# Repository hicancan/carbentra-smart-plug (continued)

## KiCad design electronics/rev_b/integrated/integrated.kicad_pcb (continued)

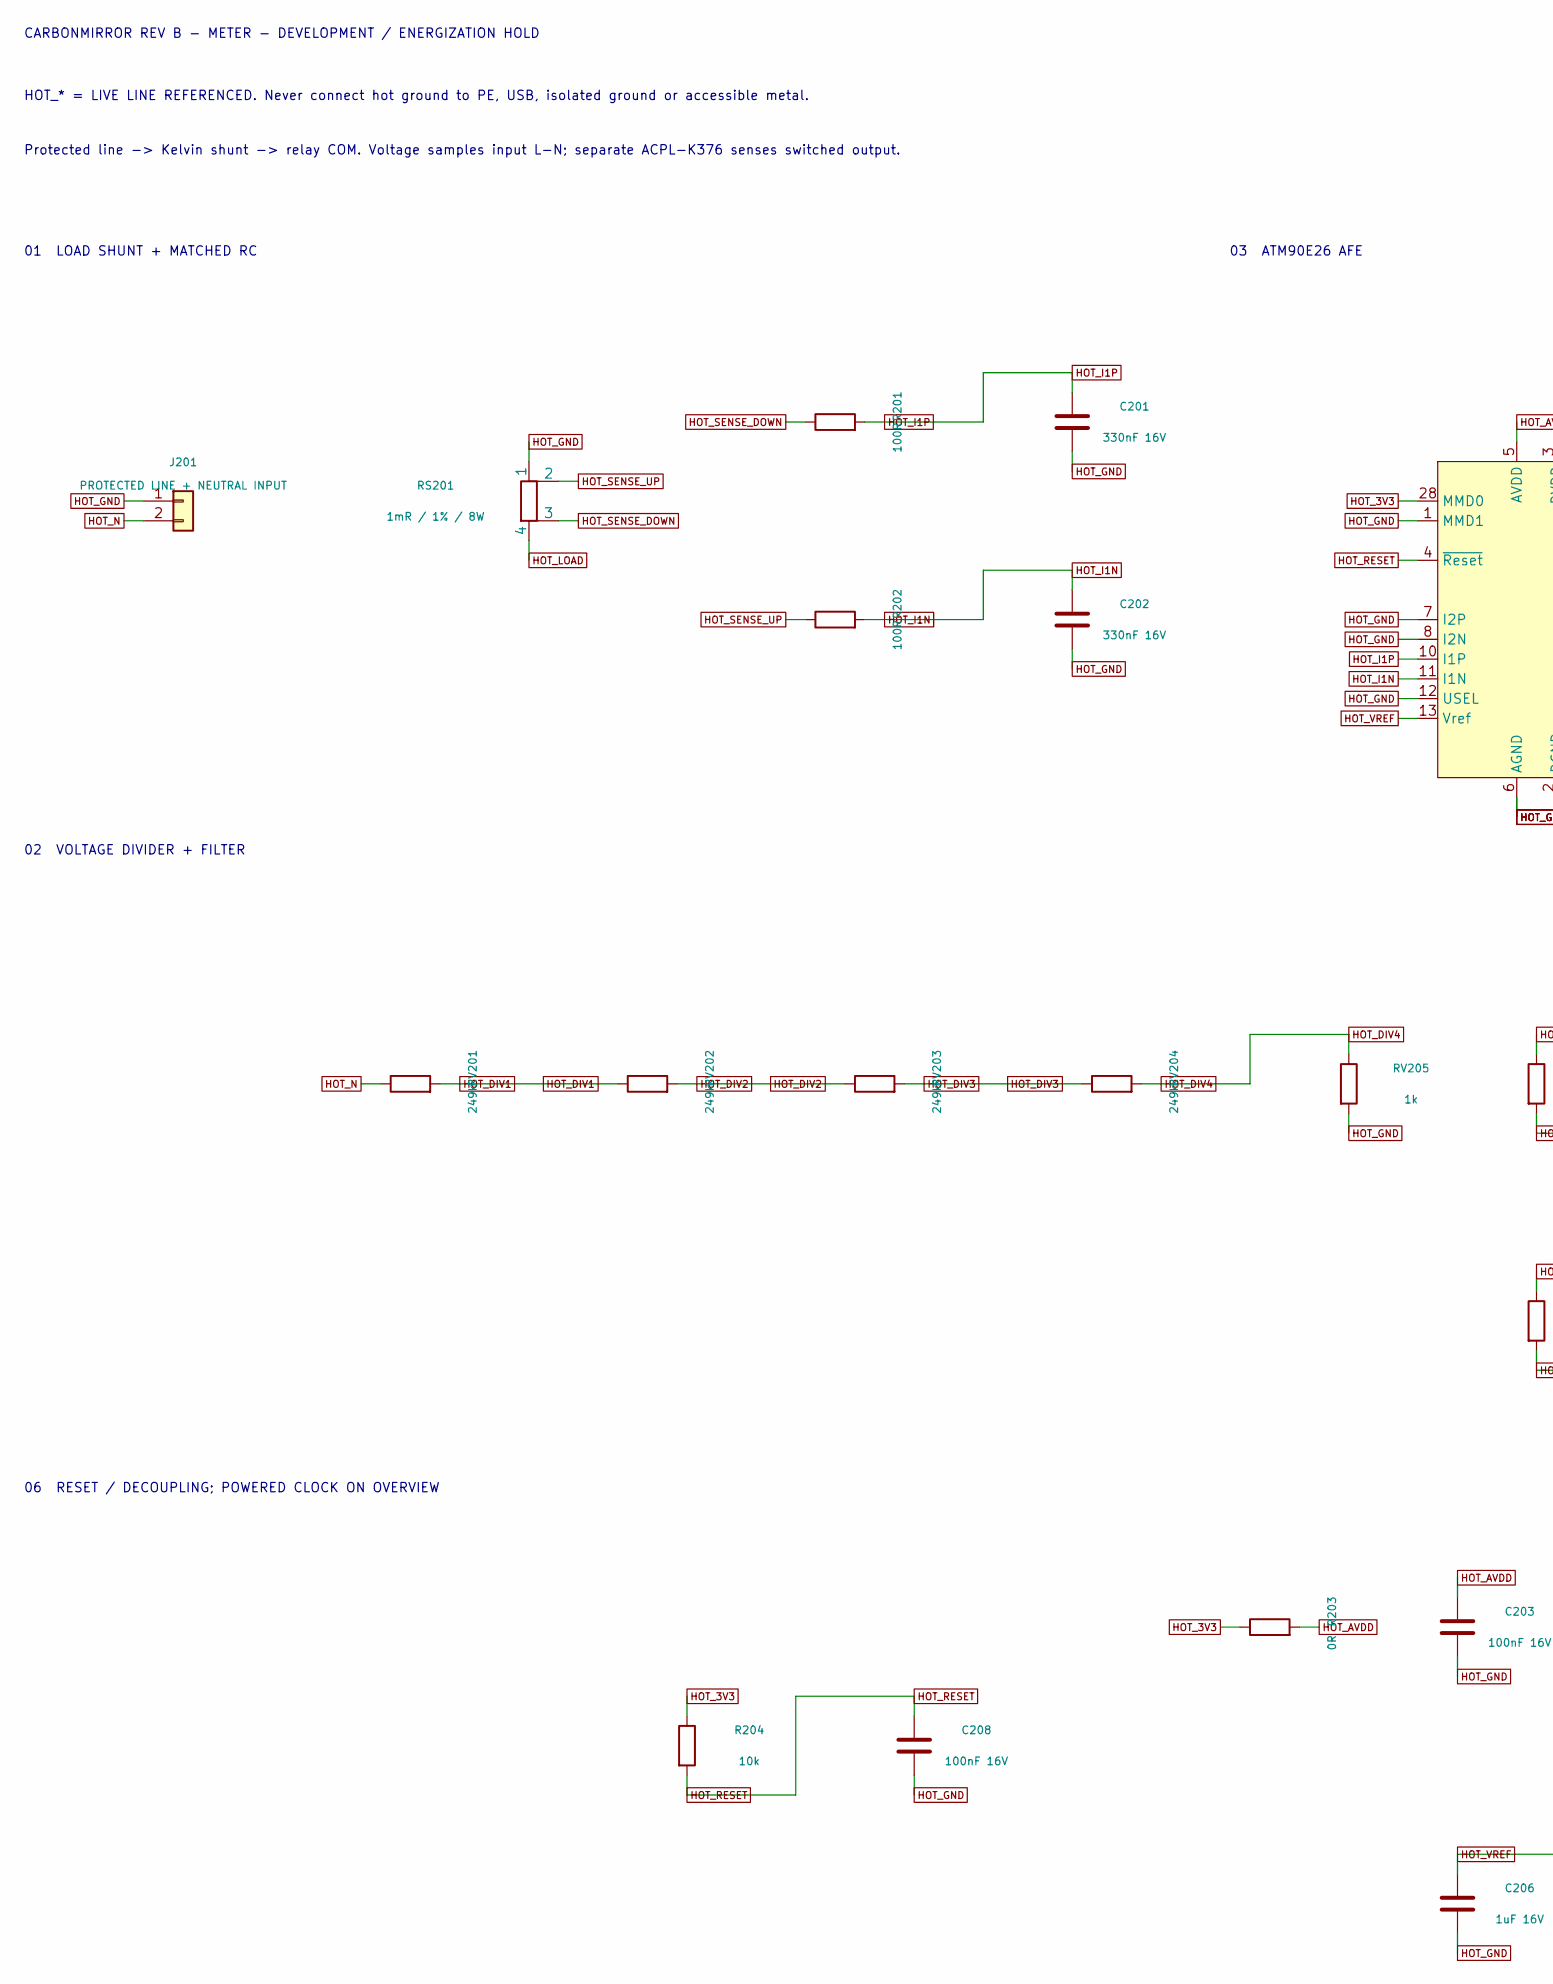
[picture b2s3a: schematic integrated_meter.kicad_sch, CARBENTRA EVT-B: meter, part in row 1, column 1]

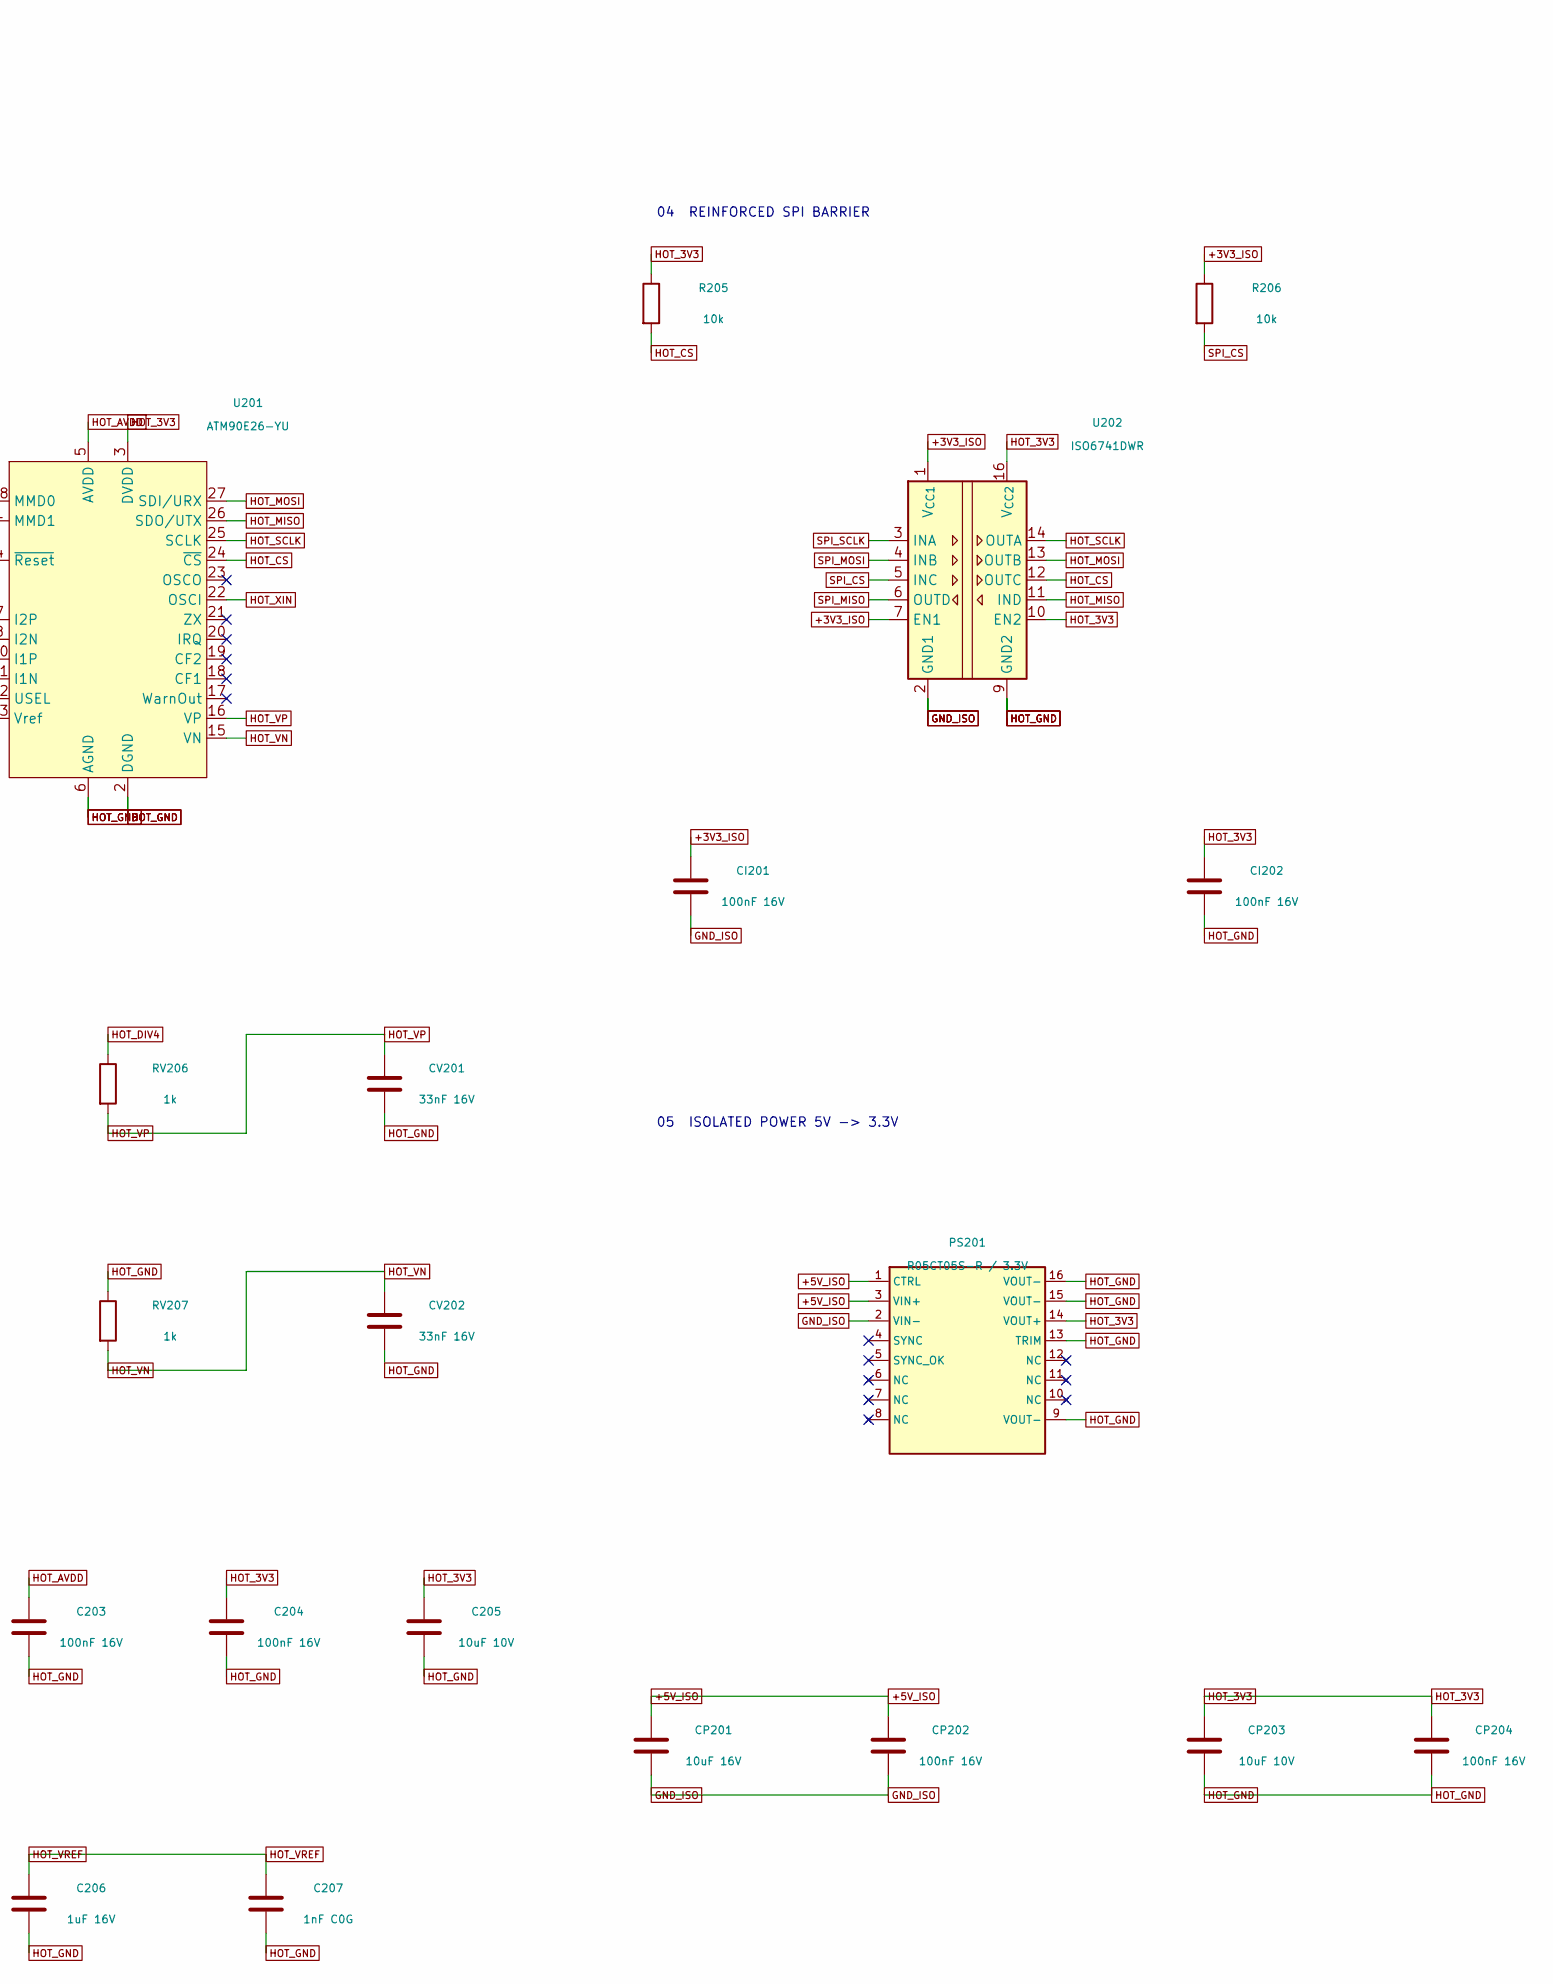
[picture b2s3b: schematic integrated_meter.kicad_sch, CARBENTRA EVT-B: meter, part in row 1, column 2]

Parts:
C201, C202: 330nF 16V; C_0805_2012Metric
C203, C204, C208: 100nF 16V; C_0805_2012Metric
C205: 10uF 10V; C_0805_2012Metric
C206: 1uF 16V; C_0805_2012Metric
C207: 1nF C0G; C_0805_2012Metric
CI201, CI202: 100nF 16V; C_0805_2012Metric
CP201: 10uF 16V; C_0805_2012Metric
CP202, CP204: 100nF 16V; C_0805_2012Metric
CP203: 10uF 10V; C_0805_2012Metric
CV201, CV202: 33nF 16V; C_0805_2012Metric
J201: PROTECTED LINE + NEUTRAL INPUT; MKDS5_2_7p62
PS201: R05CT05S-R / 3.3V; R05CT05S_8p1
R201, R202: 100R; R_0603_1608Metric
R203: 0R; R_0805_2012Metric
R204, R205, R206: 10k; R_0805_2012Metric
RS201: 1mR / 1% / 8W; CSS4J_4026
RV201, RV202, RV203, RV204: 249k; R_1206_3216Metric
RV205, RV206, RV207: 1k; R_0805_2012Metric
U201: ATM90E26-YU; SSOP-28_5.3x10.2mm_P0.65mm
U202: ISO6741DWR; ISO6741_DW_8p1

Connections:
+3V3_ISO: CI201.1, R206.1, U202.1 (V_{CC1}), U202.7 (EN1); also elsewhere on the board
+5V_ISO: CP201.1, CP202.1, PS201.1 (CTRL), PS201.3 (VIN+); also elsewhere on the board
GND_ISO: CI201.2, CP201.2, CP202.2, PS201.2 (VIN-), U202.2 (GND1), U202.8 (GND1); also elsewhere on the board
HOT_3V3: C204.1, C205.1, CI202.1, CP203.1, CP204.1, PS201.14 (VOUT+), R203.1, R204.1, R205.1, U201.3 (DVDD), U201.28 (MMD0), U202.10 (EN2), U202.16 (V_{CC2}); also elsewhere on the board
HOT_AVDD: C203.1, R203.2, U201.5 (AVDD)
HOT_CS: R205.2, U201.24 (~CS), U202.12 (OUTC)
HOT_DIV1: RV201.2, RV202.1
HOT_DIV2: RV202.2, RV203.1
HOT_DIV3: RV203.2, RV204.1
HOT_DIV4: RV204.2, RV205.1, RV206.1
HOT_GND: C201.2, C202.2, C203.2, C204.2, C205.2, C206.2, C207.2, C208.2, CI202.2, CP203.2, CP204.2, CV201.2, CV202.2, J201.1, PS201.9 (VOUT-), PS201.13 (TRIM), PS201.15 (VOUT-), PS201.16 (VOUT-), RS201.1, RV205.2, RV207.1, U201.1 (MMD1), U201.2 (DGND), U201.6 (AGND), U201.7 (I2P), U201.8 (I2N), U201.9 (DGND), U201.12 (USEL), U201.14 (AGND), U202.9 (GND2), U202.15 (GND2); also elsewhere on the board
HOT_I1N: C202.1, R202.2, U201.11 (I1N)
HOT_I1P: C201.1, R201.2, U201.10 (I1P)
HOT_LOAD: RS201.4; also elsewhere on the board
HOT_MISO: U201.26 (SDO/UTX), U202.11 (IND)
HOT_MOSI: U201.27 (SDI/URX), U202.13 (OUTB)
HOT_N: J201.2, RV201.1; also elsewhere on the board
HOT_RESET: C208.1, R204.2, U201.4 (~Reset)
HOT_SCLK: U201.25 (SCLK), U202.14 (OUTA)
HOT_SENSE_DOWN: R201.1, RS201.3
HOT_SENSE_UP: R202.1, RS201.2
HOT_VN: CV202.1, RV207.2, U201.15 (VN)
HOT_VP: CV201.1, RV206.2, U201.16 (VP)
HOT_VREF: C206.1, C207.1, U201.13 (Vref)
HOT_XIN: U201.22 (OSCI); also elsewhere on the board
SPI_CS: R206.2, U202.5 (INC); also elsewhere on the board
SPI_MISO: U202.6 (OUTD); also elsewhere on the board
SPI_MOSI: U202.4 (INB); also elsewhere on the board
SPI_SCLK: U202.3 (INA); also elsewhere on the board

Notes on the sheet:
CARBONMIRROR REV B - METER - DEVELOPMENT / ENERGIZATION HOLD
HOT_* = LIVE LINE REFERENCED. Never connect hot ground to PE, USB, isolated ground or accessible metal.
Protected line -> Kelvin shunt -> relay COM. Voltage samples input L-N; separate ACPL-K376 senses switched output.
01 LOAD SHUNT + MATCHED RC
02 VOLTAGE DIVIDER + FILTER
03 ATM90E26 AFE
04 REINFORCED SPI BARRIER
05 ISOLATED POWER 5V -> 3.3V
06 RESET / DECOUPLING; POWERED CLOCK ON OVERVIEW

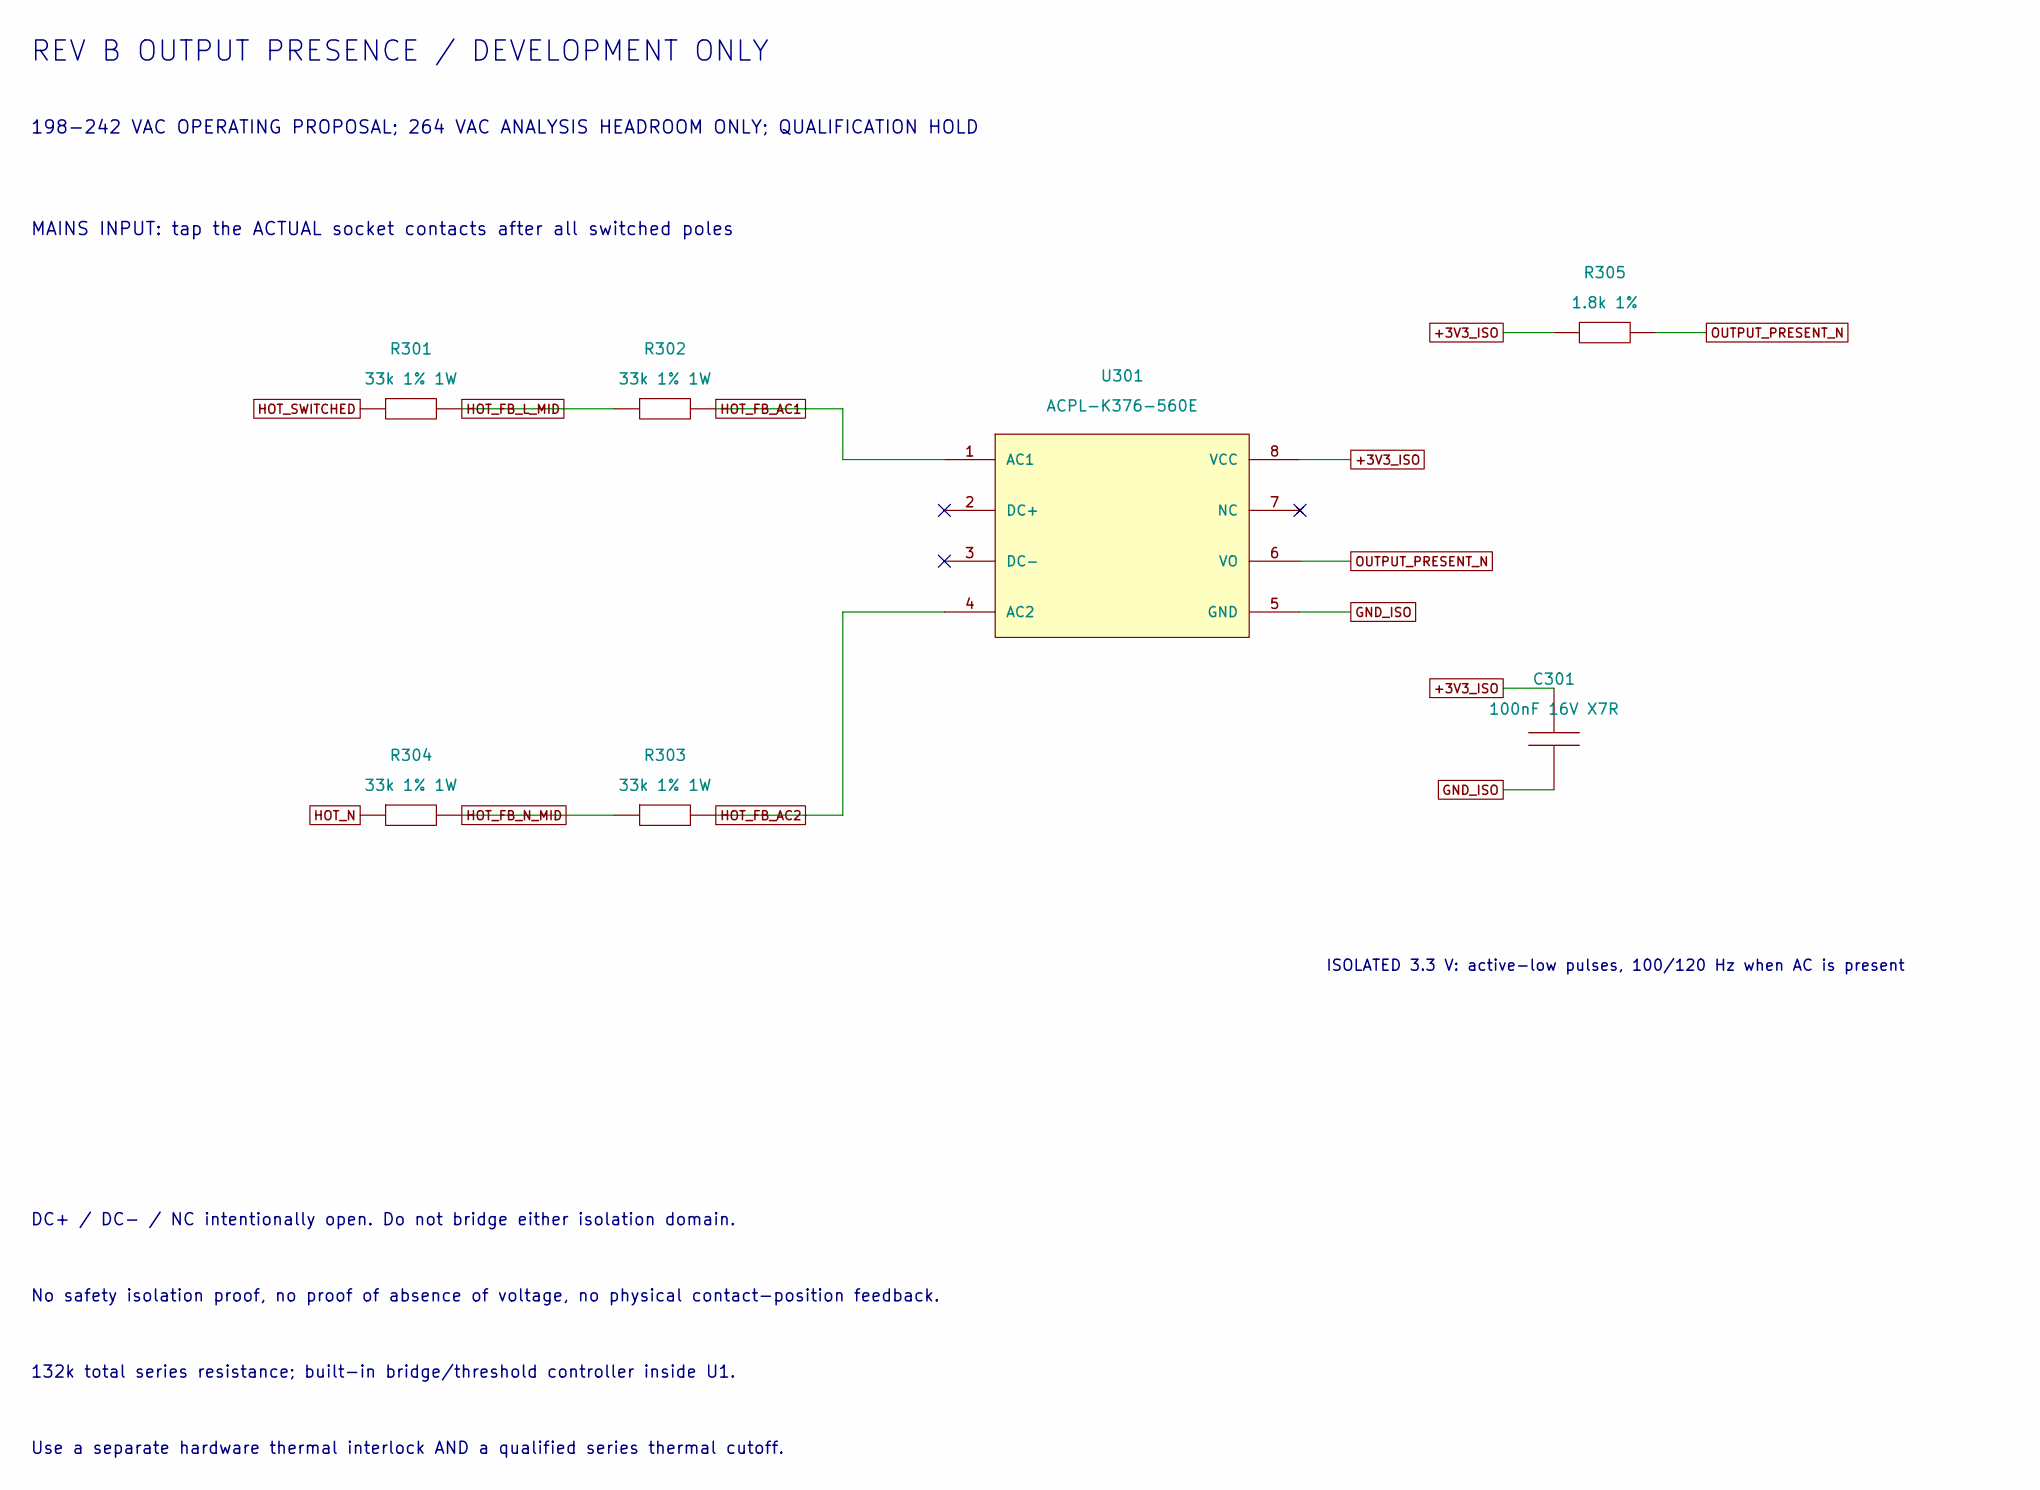
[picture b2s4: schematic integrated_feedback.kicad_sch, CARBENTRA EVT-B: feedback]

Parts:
C301: 100nF 16V X7R; C_0603_1608Metric
R301, R302, R303, R304: 33k 1% 1W; PR01_P10.16
R305: 1.8k 1%; R_0603_1608Metric
U301: ACPL-K376-560E; SSO8_ACPL_K376

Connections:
+3V3_ISO: C301.1, R305.1, U301.8 (VCC); also elsewhere on the board
GND_ISO: C301.2, U301.5 (GND); also elsewhere on the board
HOT_FB_AC1: R302.2, U301.1 (AC1)
HOT_FB_AC2: R303.2, U301.4 (AC2)
HOT_FB_L_MID: R301.2, R302.1
HOT_FB_N_MID: R303.1, R304.2
HOT_N: R304.1; also elsewhere on the board
HOT_SWITCHED: R301.1; also elsewhere on the board
OUTPUT_PRESENT_N: R305.2, U301.6 (VO); also elsewhere on the board

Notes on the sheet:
REV B OUTPUT PRESENCE / DEVELOPMENT ONLY
198-242 VAC OPERATING PROPOSAL; 264 VAC ANALYSIS HEADROOM ONLY; QUALIFICATION HOLD
MAINS INPUT: tap the ACTUAL socket contacts after all switched poles
ISOLATED 3.3 V: active-low pulses, 100/120 Hz when AC is present
DC+ / DC- / NC intentionally open. Do not bridge either isolation domain.
No safety isolation proof, no proof of absence of voltage, no physical contact-position feedback.
132k total series resistance; built-in bridge/threshold controller inside U1.
Use a separate hardware thermal interlock AND a qualified series thermal cutoff.

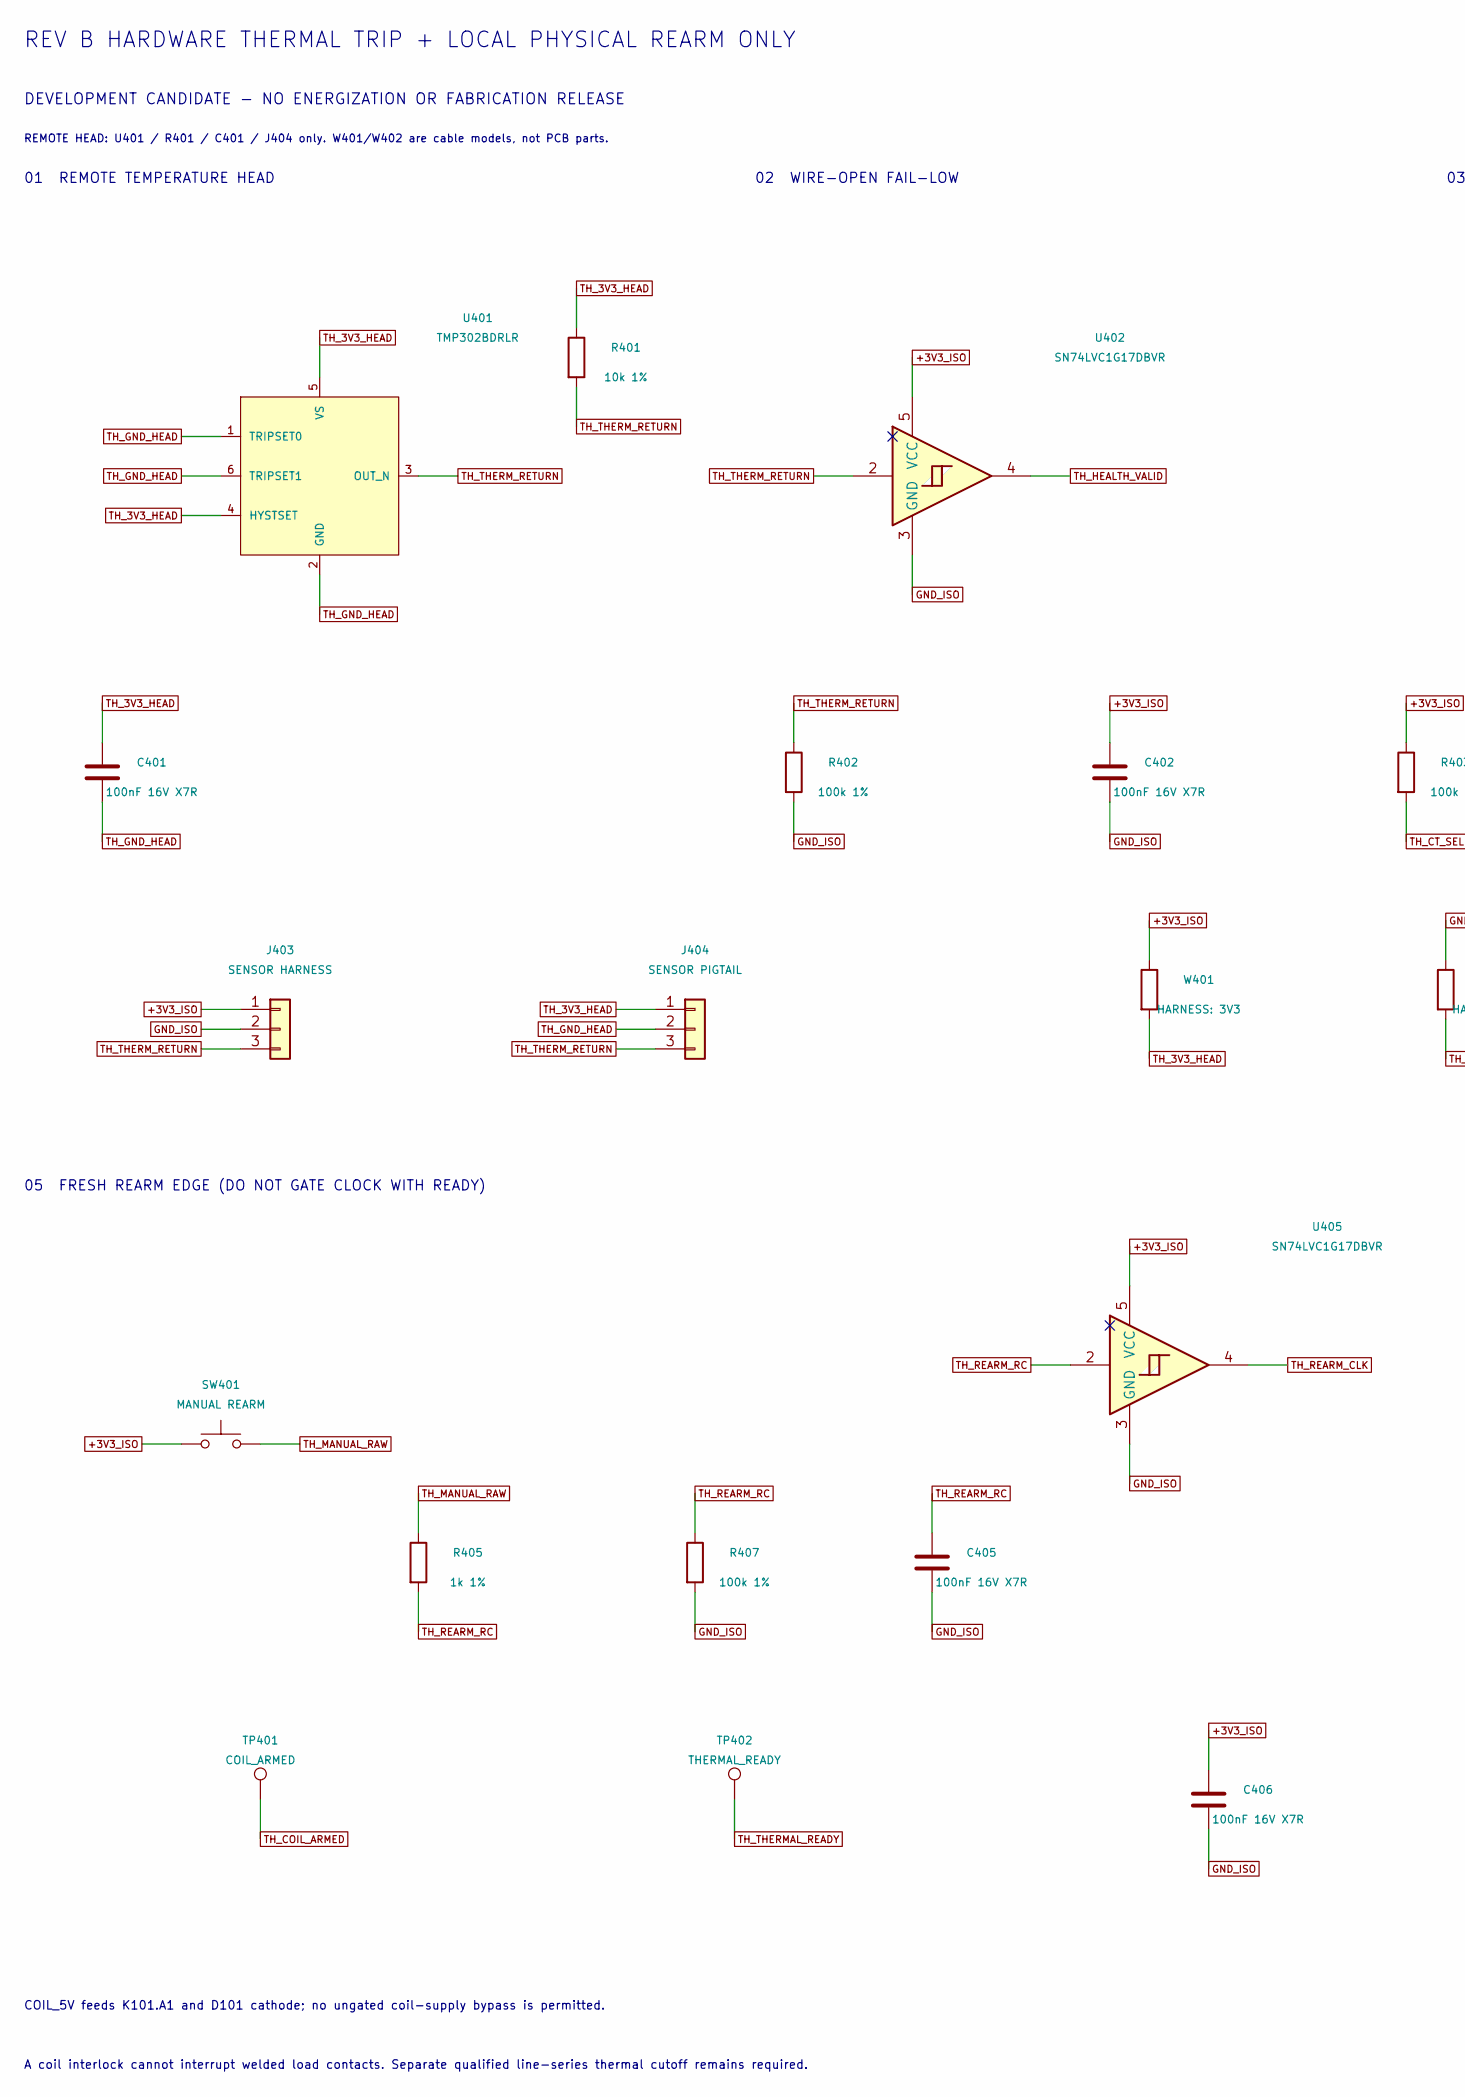
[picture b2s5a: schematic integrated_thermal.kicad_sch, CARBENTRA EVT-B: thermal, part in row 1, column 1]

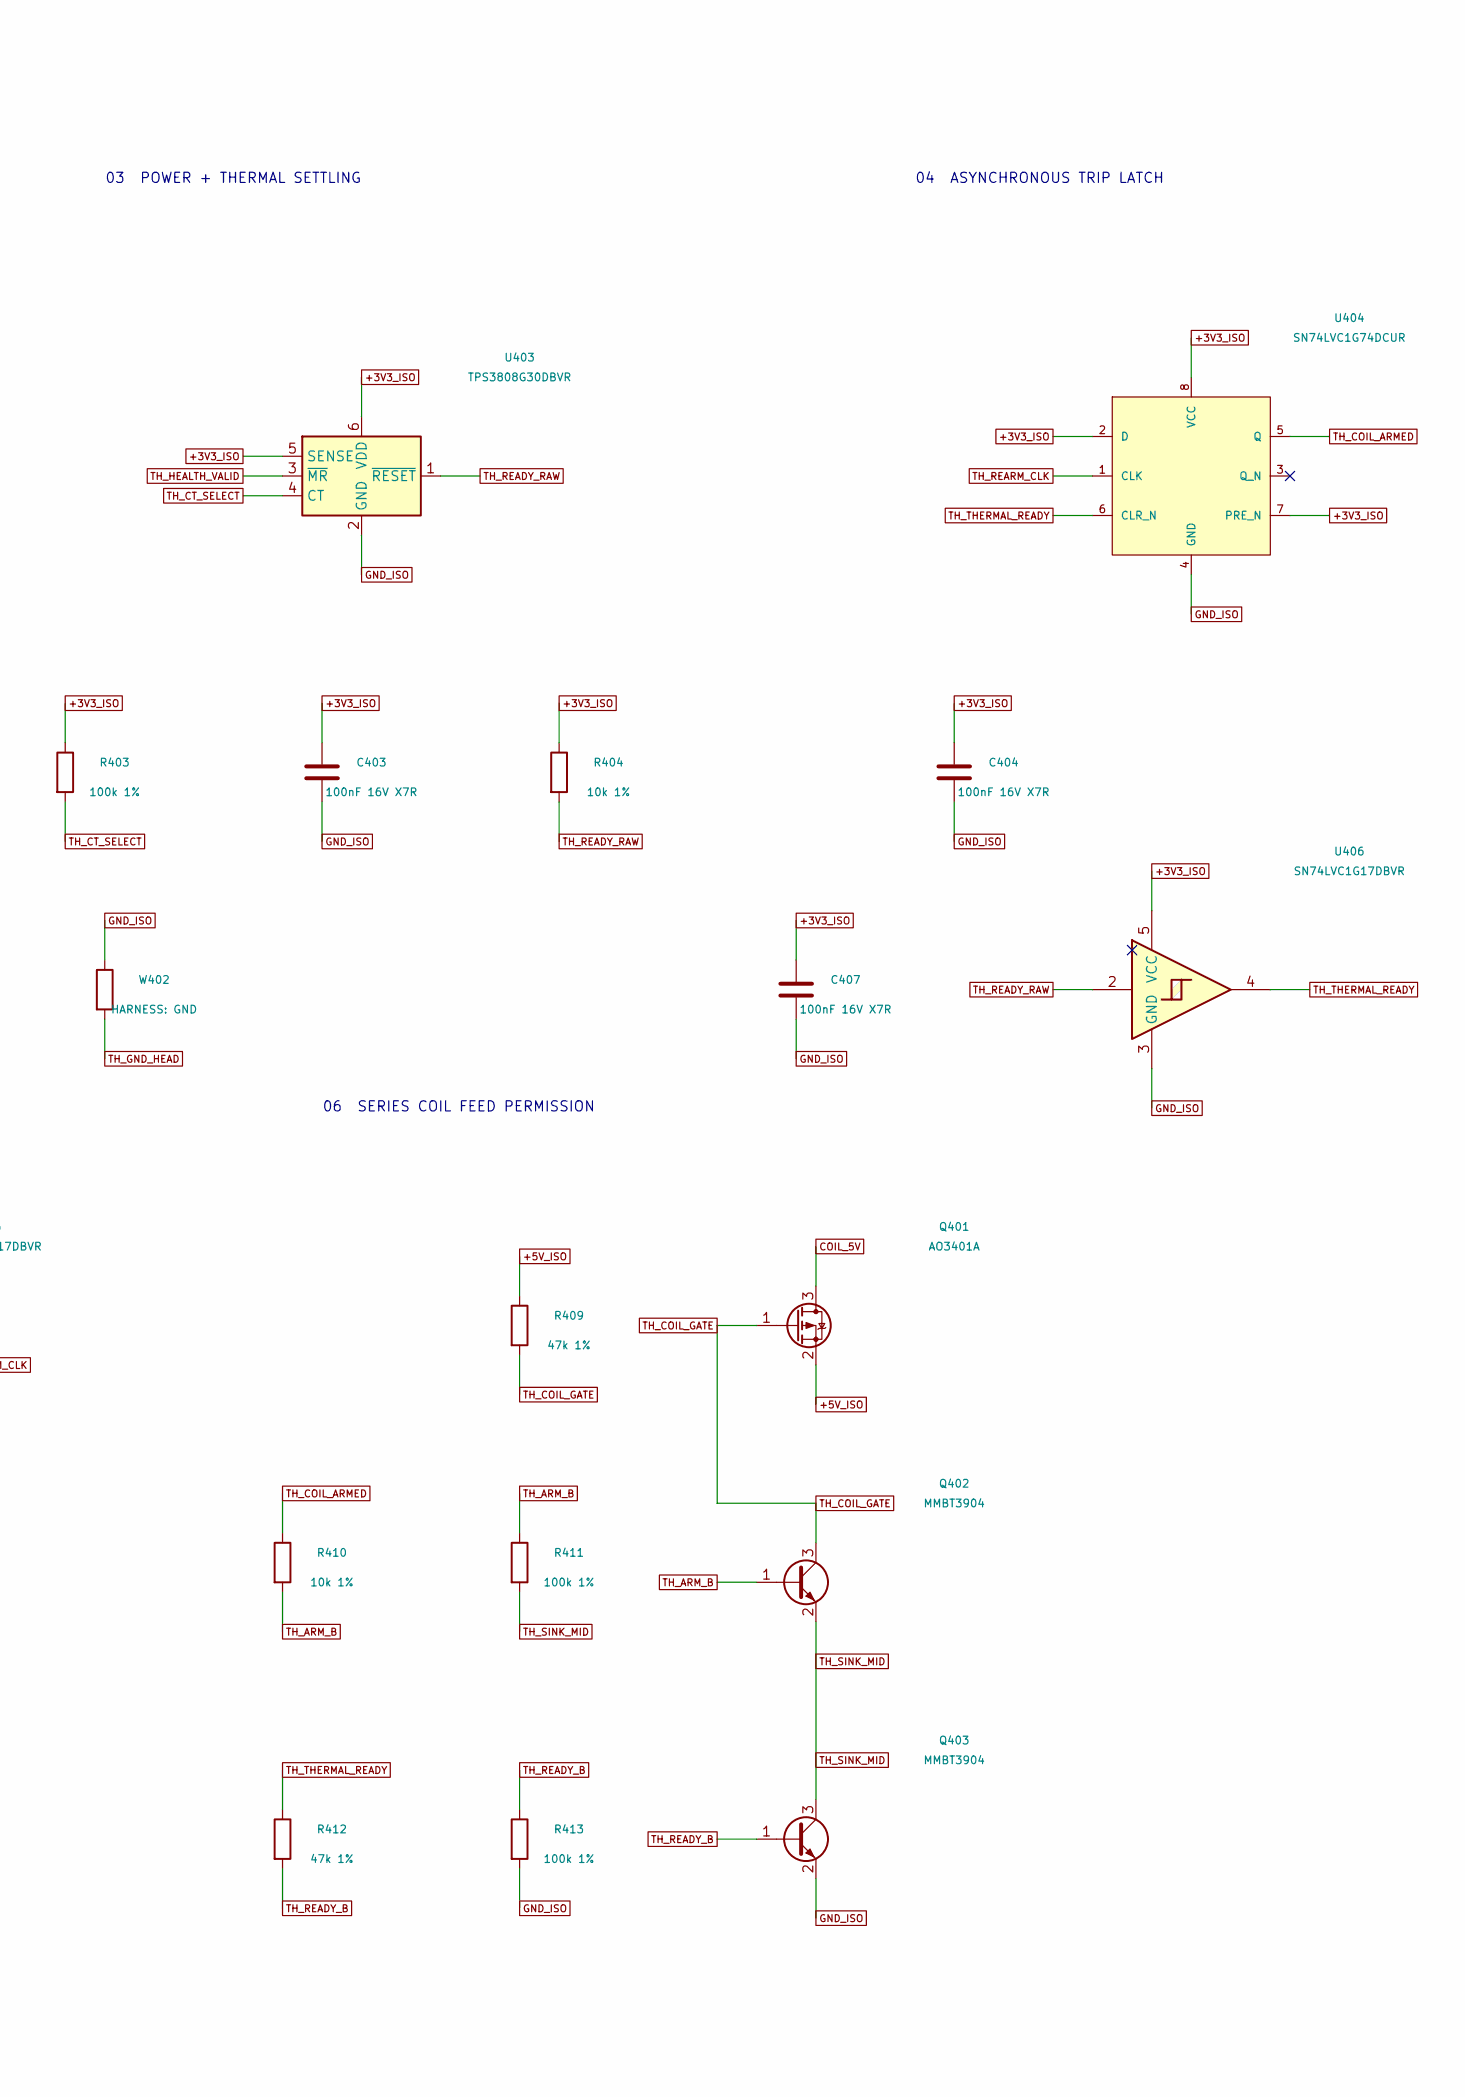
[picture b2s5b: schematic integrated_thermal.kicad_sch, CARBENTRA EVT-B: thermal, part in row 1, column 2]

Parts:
C401, C402, C403, C404, C405, C406, C407: 100nF 16V X7R; C_0603_1608Metric
J403: SENSOR HARNESS; PinHeader_1x03_P2.54mm_Vertical
J404: SENSOR PIGTAIL; Sensor_Pigtail_3xP2.54
Q401: AO3401A; SOT-23
Q402, Q403: MMBT3904; SOT-23
R401, R404, R410: 10k 1%; R_0603_1608Metric
R402, R403, R407, R411, R413: 100k 1%; R_0603_1608Metric
R405: 1k 1%; R_0603_1608Metric
R409, R412: 47k 1%; R_0603_1608Metric
SW401: MANUAL REARM; SW_PUSH_6mm
TP401: COIL_ARMED; TestPoint_Pad_D1.0mm
TP402: THERMAL_READY; TestPoint_Pad_D1.0mm
U401: TMP302BDRLR; SOT-563
U402, U405, U406: SN74LVC1G17DBVR; SOT-23-5
U403: TPS3808G30DBVR; SOT-23-6
U404: SN74LVC1G74DCUR; VSSOP-8_2.3x2mm_P0.5mm
W401: HARNESS: 3V3; R_0603_1608Metric
W402: HARNESS: GND; R_0603_1608Metric

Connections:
+3V3_ISO: C402.1, C403.1, C404.1, C406.1, C407.1, J403.1, R403.1, R404.1, SW401.1, U402.5 (VCC), U403.5 (SENSE), U403.6 (VDD), U404.2 (D), U404.7 (PRE_N), U404.8 (VCC), U405.5 (VCC), U406.5 (VCC), W401.1; also elsewhere on the board
+5V_ISO: Q401.2 (S), R409.1; also elsewhere on the board
COIL_5V: Q401.3 (D); also elsewhere on the board
GND_ISO: C402.2, C403.2, C404.2, C405.2, C406.2, C407.2, J403.2, Q403.2 (E), R402.2, R407.2, R413.2, U402.3 (GND), U403.2 (GND), U404.4 (GND), U405.3 (GND), U406.3 (GND), W402.1; also elsewhere on the board
unnamed: C401.1, J404.1, R401.1, U401.4 (HYSTSET), U401.5 (VS), W401.2
unnamed: C401.2, J404.2, U401.1 (TRIPSET0), U401.2 (GND), U401.6 (TRIPSET1), W402.2
TH_ARM_B: Q402.1 (B), R410.2, R411.1
TH_COIL_ARMED: R410.1, TP401.1, U404.5 (Q)
TH_COIL_GATE: Q401.1 (G), Q402.3 (C), R409.2
TH_CT_SELECT: R403.2, U403.4 (CT)
TH_HEALTH_VALID: U402.4, U403.3 (~MR)
TH_MANUAL_RAW: R405.1, SW401.2
TH_READY_B: Q403.1 (B), R412.2, R413.1
TH_READY_RAW: R404.2, U403.1 (~RESET), U406.2
TH_REARM_CLK: U404.1 (CLK), U405.4
TH_REARM_RC: C405.1, R405.2, R407.1, U405.2
TH_SINK_MID: Q402.2 (E), Q403.3 (C), R411.2
TH_THERMAL_READY: R412.1, TP402.1, U404.6 (CLR_N), U406.4
TH_THERM_RETURN: J403.3, J404.3, R401.2, R402.1, U401.3 (OUT_N), U402.2

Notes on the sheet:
REV B HARDWARE THERMAL TRIP + LOCAL PHYSICAL REARM ONLY
DEVELOPMENT CANDIDATE - NO ENERGIZATION OR FABRICATION RELEASE
01 REMOTE TEMPERATURE HEAD
02 WIRE-OPEN FAIL-LOW
03 POWER + THERMAL SETTLING
04 ASYNCHRONOUS TRIP LATCH
05 FRESH REARM EDGE (DO NOT GATE CLOCK WITH READY)
06 SERIES COIL FEED PERMISSION
COIL_5V feeds K101.A1 and D101 cathode; no ungated coil-supply bypass is permitted.
A coil interlock cannot interrupt welded load contacts. Separate qualified line-series thermal cutoff remains required.
REMOTE HEAD: U401 / R401 / C401 / J404 only. W401/W402 are cable models, not PCB parts.
